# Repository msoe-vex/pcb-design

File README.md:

# PCB and Circuitry Design Repository
This repository is dedicated to storing files required for designing and creating PCBs for our robots. Different projects are put in separate folders, and an included "README.md" file should be included with each project to explain the purpose of each.

## Software Installation
These projects largely use the KiCAD application for circuitry and PCB design. This software can be installed from the following link: 

https://downloads.kicad.org/kicad/windows/explore/nightlies/download/kicad-msvc.r24754.1860893d63-x86_64.exe

**NOTE: We will be using a nightly version until KiCAD 6.00 is released later this year!**

Other versions for various OS platforms can also be found on their website.

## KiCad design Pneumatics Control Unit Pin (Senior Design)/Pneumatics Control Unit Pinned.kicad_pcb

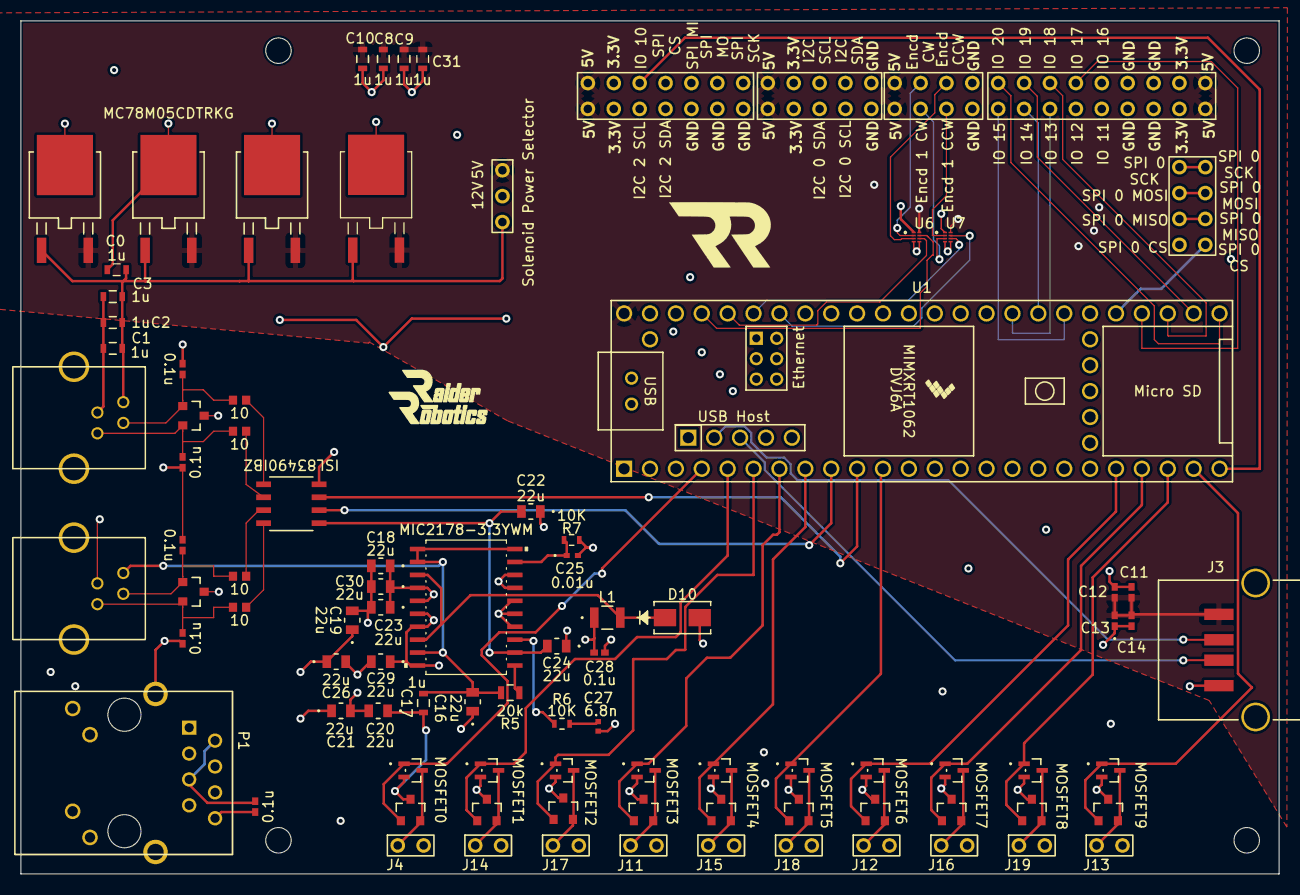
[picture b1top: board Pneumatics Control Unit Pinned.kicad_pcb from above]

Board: 4 copper layers, 123.4 x 83.7 mm, 96 parts (0 on the bottom side), 82 nets.

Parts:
C0, C1, C2, C3, C8, C9, C10, C17, C31: 1u; C1608X7R1C105K080AC
C4, C5, C6, C7, C11, C12, C15, C28: 0.1u; 0402YC104KAT2A
C13, C14: 10n; 0402YC103KAT2A
C16, C18, C19, C20, C21, C22, C23, C24, C26, C29, C30: 22u; CL21A226MQQNNNE
C25: 0.01u; CL05B103KO5NNNC
C27: 6.8n; 0402B682K500CT
D1, D2, D3, D4, D5, D6, D7, D8, D9, D11, D12, D13: PESD1FLEX,215; PESD1FLEX215
D10: CDBA340-HF
H1, H2, H3, H4: MountingHole; MountingHole_2.5mm
J1: RX_PORT; MTJ-642BX2
J2: TX_PORT; MTJ-642BX2
J3: 87583-2010BLF
J4, J11, J12, J13, J14, J15, J16, J17, J18, J19: Conn_01x02_Male; Conn_1x2
J5: GPIO Bank 0; Conn_2x7
J6: SPI 0; Conn_2x4
J7: Solenoid Power Selector; Conn_1x3
J8: GPIO Bank 1; Conn_2x9
J9: I2C 1-2; Conn_2x5
J10: Encoder; Conn_2x4
L1: 33u; LB3218T330K
MOSFET0, MOSFET1, MOSFET2, MOSFET3, MOSFET4, MOSFET5, MOSFET6, MOSFET7, MOSFET8, MOSFET9: SSM3K7002KFU
P1: J1B1211CCD
R1, R2, R3, R4: 10; RNCP0603FTD10R0
R5: 20k; SR1-0805-320
R6, R7: 10K; SR1-0603-310
U0, U2, U3, U4: MC78M05CDTRKG
U1: Teensy4.1; Teensy41
U5: ISL83490IBZ
U6, U7: 74AXP2T3407GSX
U8: MIC2178-3.3YWM; MIC2178-33YWM

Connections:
+3V3: C18.2, C19.2, C20.2, C21.2, C22.2, C23.2, C24.2, C26.2, C28.2, C29.2, C30.2, J5.2, J5.9, J8.2, J8.11, J9.2, J9.7, L1.1, U5.1 (VCC), U6.1 (VCCI), U7.1 (VCCI), U8.12 (FB)
+5V: C8.2, C9.2, C10.2, C11.2, C12.2, C13.2, C14.2, C31.2, J3.4 (VCC), J5.1, J5.8, J7.1, J8.1, J8.10, J9.1, J9.6, J10.1, J10.5, U0.3 (OUTPUT), U1.48 (VIN), U2.3 (OUTPUT), U3.3 (OUTPUT), U4.3 (OUTPUT), U6.8 (VCCO), U7.8 (VCCO)
/Encoder_0_CCW: J10.7, U6.3 (2A)
/Encoder_0_CW: J10.6, U6.2 (1A)
/Encoder_1_CCW: J10.3, U7.2 (1A)
/Encoder_1_CW: J10.2, U7.3 (2A)
/GPIO_0: D3.1, MOSFET0.1 (GATE), U1.4 (2_OUT2)
/GPIO_1: D7.1, MOSFET1.1 (GATE), U1.5 (3_LRCLK2)
/GPIO_2: D11.1, MOSFET2.1 (GATE), U1.6 (4_BCLK2)
/GPIO_3: D4.1, MOSFET3.1 (GATE), U1.7 (5_IN2)
/GPIO_4: D8.1, MOSFET4.1 (GATE), U1.8 (6_OUT1D)
/GPIO_5: D12.1, MOSFET5.1 (GATE), U1.11 (9_OUT1C)
/GPIO_6: D5.1, MOSFET6.1 (GATE), U1.20 (28_RX7)
/GPIO_7: D9.1, MOSFET7.1 (GATE), U1.21 (29_TX7)
/GPIO_8: D13.1, MOSFET8.1 (GATE), U1.22 (30_CRX3)
/GPIO_9: D6.1, MOSFET9.1 (GATE), U1.23 (31_CTX3)
/GPIO_10: J5.10, U1.24 (32_OUT1B)
/GPIO_11: J8.14, U1.37 (15_A1_RX3_SPDIF_IN)
/GPIO_12: J8.15, U1.36 (14_A0_TX3_SPDIF_OUT)
/GPIO_13: J8.16, U1.33 (41_A17)
/GPIO_14: J8.17, U1.32 (40_A16)
/GPIO_15: J8.18, U1.31 (39_MISO1_OUT1A)
/GPIO_16: J8.5, U1.30 (38_CS1_IN1)
/GPIO_17: J8.6, U1.28 (36_CS)
/GPIO_18: J8.7, U1.27 (35_TX8)
/GPIO_19: J8.8, U1.26 (34_RX8)
/GPIO_20: J8.9, U1.25 (33_MCLK2)
/I2C_0_SCL: J9.4, U1.41 (19_A5_SCL)
/I2C_0_SDA: J9.3, U1.40 (18_A4_SDA)
/I2C_1_SCL: J9.8, U1.38 (16_A2_RX4_SCL1)
/I2C_1_SDA: J9.9, U1.39 (17_A3_TX4_SDA1)
/I2C_2_SCL: J5.3, U1.16 (24_A10_TX6_SCL2)
/I2C_2_SDA: J5.4, U1.17 (25_A11_RX6_SDA2)
/LED_Ethernet: P1.10 (GRN+), U1.61 (LED)
/R+_Ethernet: P1.4 (RD+), U1.60 (R+)
/R-_Ethernet: P1.6 (RD-), U1.65 (R-)
/RS485_A_12V: C16.2, C17.2, J1.4, R5.2, U8.1 (VIN), U8.2 (VIN), U8.9 (VIN), U8.20 (EN)
/RS485_B_12V: C0.2, C1.2, C2.2, C3.2, J2.4, J7.3, U0.1 (INPUT), U2.1 (INPUT), U3.1 (INPUT), U4.1 (INPUT)
/RS485_RXD: U1.10 (8_TX2_IN1), U5.3 (DI)
/RS485_TXD: U1.9 (7_RX2_OUT1A), U5.2 (RO)
/SPI_0_CS: J6.4, J6.8, U1.12 (10_CS_MQSR), U1.29 (37_CS)
/SPI_0_MISO: J6.3, J6.7, U1.14 (12_MISO_MQSL)
/SPI_0_MOSI: J6.2, J6.6, U1.13 (11_MOSI_CTX1)
/SPI_0_SCK: J6.1, J6.5, U1.35 (13_SCK_LED)
/SPI_1_CS: J5.11, U1.2 (0_RX1_CRX2_CS1)
/SPI_1_MISO1: J5.12, U1.3 (1_TX1_CTX2_MISO1)
/SPI_1_MOSI1: J5.13, U1.18 (26_A12_MOSI1)
/SPI_1_SCK: J5.14, U1.19 (27_A13_SCK1)
/Solenoid_Power: J4.2, J7.2, J11.2, J12.2, J13.2, J14.2, J15.2, J16.2, J17.2, J18.2, J19.2
/T+_Ethernet: P1.1 (TD+), U1.63 (T+)
/T-_Ethernet: P1.3 (TD-), U1.62 (T-)
/USB_D+: J3.2 (D+), U1.57 (D+)
/USB_D-: J3.3 (D-), U1.56 (D-)
GND: C0.1, C1.1, C2.1, C3.1, C4.1, C5.1, C6.1, C7.1, C8.1, C9.1, C10.1, C11.1, C12.1, C13.1, C14.1, C15.1, C16.1, C17.1, C18.1, C19.1, C20.1, C21.1, C22.1, C23.1, C24.1, C25.2, C26.1, C27.1, C28.1, C29.1, C30.1, C31.1, D1.3, D2.3, D3.3, D4.3, D5.3, D6.3, D7.3, D8.3, D9.3, D10.2, D11.3, D12.3, D13.3, J1.3, J2.3, J3.1 (GND), J5.5, J5.6, J5.7, J8.3, J8.4, J8.12, J8.13, J9.5, J9.10, J10.4, J10.8, MOSFET0.2 (SOURCE), MOSFET1.2 (SOURCE), MOSFET2.2 (SOURCE), MOSFET3.2 (SOURCE), MOSFET4.2 (SOURCE), MOSFET5.2 (SOURCE), MOSFET6.2 (SOURCE), MOSFET7.2 (SOURCE), MOSFET8.2 (SOURCE), MOSFET9.2 (SOURCE), P1.7 (NC), P1.8 (GH_GND@1), P1.9 (GRN-), P1.11 (YLW-), P1.12 (YLW+), P1.13 (CH_GND@2), P1.14 (CH_GND@3), R7.2, U0.4 (GROUND), U1.1 (GND), U1.34 (GND), U1.47 (GND), U1.50 (VBAT), U1.51 (3V3), U1.52 (GND), U1.53 (PROGRAM), U1.54 (ON_OFF), U1.58 (GND), U1.59 (GND), U1.64 (GND), U2.4 (GROUND), U3.4 (GROUND), U4.4 (GROUND), U5.4 (GND), U6.4 (GND), U6.5 (GND), U7.4 (GND), U7.5 (GND), U8.4 (PGND), U8.5 (PGND), U8.6 (PGND), U8.7 (PGND), U8.10 (*PWM), U8.14 (SGND), U8.15 (SGND), U8.16 (SGND), U8.17 (SGND), U8.18 (SYNC)
unnamed: C4.2, D1.1, J1.2, R2.1
unnamed: C5.2, D2.1, J2.2, R4.1
unnamed: C6.2, D1.2, J1.1, R1.1
unnamed: C7.2, D2.2, J2.1, R3.1
unnamed: C27.2, R6.2
unnamed: D3.2, J4.1, MOSFET0.3 (DRAIN)
unnamed: D4.2, J11.1, MOSFET3.3 (DRAIN)
unnamed: D5.2, J12.1, MOSFET6.3 (DRAIN)
unnamed: D6.2, J13.1, MOSFET9.3 (DRAIN)
unnamed: D7.2, J14.1, MOSFET1.3 (DRAIN)
unnamed: D8.2, J15.1, MOSFET4.3 (DRAIN)
unnamed: D9.2, J16.1, MOSFET7.3 (DRAIN)
unnamed: D11.2, J17.1, MOSFET2.3 (DRAIN)
unnamed: D12.2, J18.1, MOSFET5.3 (DRAIN)
unnamed: D13.2, J19.1, MOSFET8.3 (DRAIN)
unnamed: C15.2, P1.2 (TCT), P1.5 (RCT)
unnamed: U1.42 (20_A6_TX5_LRCLK1), U7.7 (1Y)
unnamed: U1.43 (21_A7_RX5_BCLK1), U7.6 (2Y)
unnamed: U1.44 (22_A8_CTX1), U6.6 (2Y)
unnamed: U1.45 (23_A9_CRX1_MCLK1), U6.7 (1Y)
unnamed: R1.2, U5.8 (A)
unnamed: R2.2, U5.7 (B)
unnamed: R4.2, U5.5 (Y)
unnamed: R3.2, U5.6 (Z)
unnamed: C25.1, R7.1, U8.19 (BIAS)
unnamed: R6.1, U8.13 (COMP)
unnamed: R5.1, U8.11 (PWRGD)
unnamed: D10.1, L1.2, U8.3 (SW), U8.8 (SW)

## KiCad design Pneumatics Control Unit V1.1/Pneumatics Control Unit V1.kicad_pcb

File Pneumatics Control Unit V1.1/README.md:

# Pneumatic Control Unit
This project is dedicated to creating a board that can control 8 pneumatic devices running at either 5V or 12V from the VEX V5 brain. We take power from the smart ports to power the pneumatics, then based on the jumpers will step down the voltage to 5V or keep it at 12V. The signal sent to the board will be read by a MicoMod teensy and will then send a signal to the corresponding pneumatic device. The transmit port is for future versions.

### Project Information
This board was originally created by Nathan Roth and Asher Sprigler, with assistance provided by Andrew Kempen in the 2021-2022 VEX season.

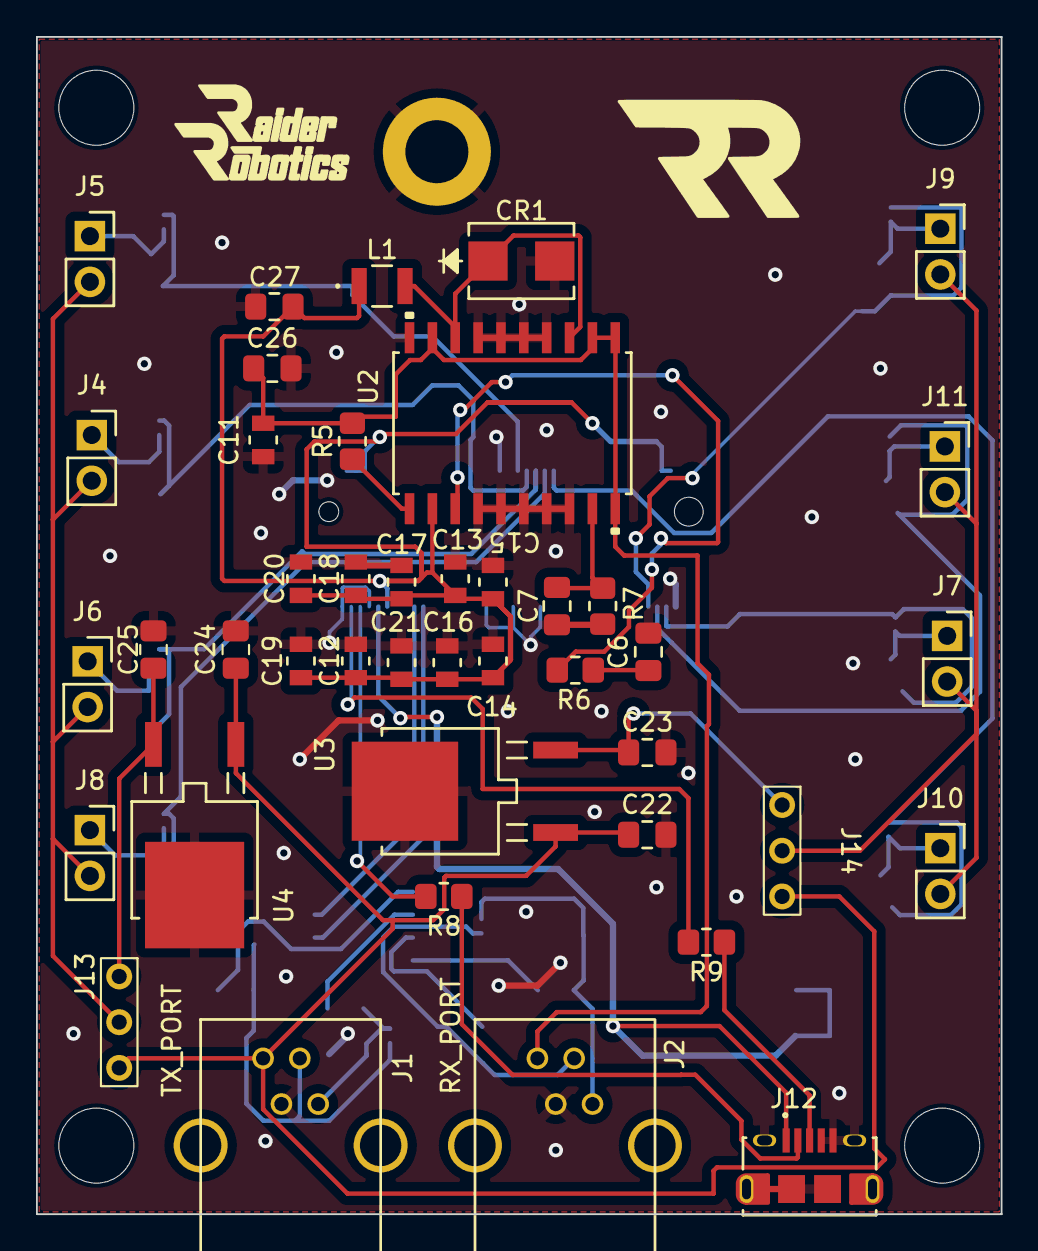
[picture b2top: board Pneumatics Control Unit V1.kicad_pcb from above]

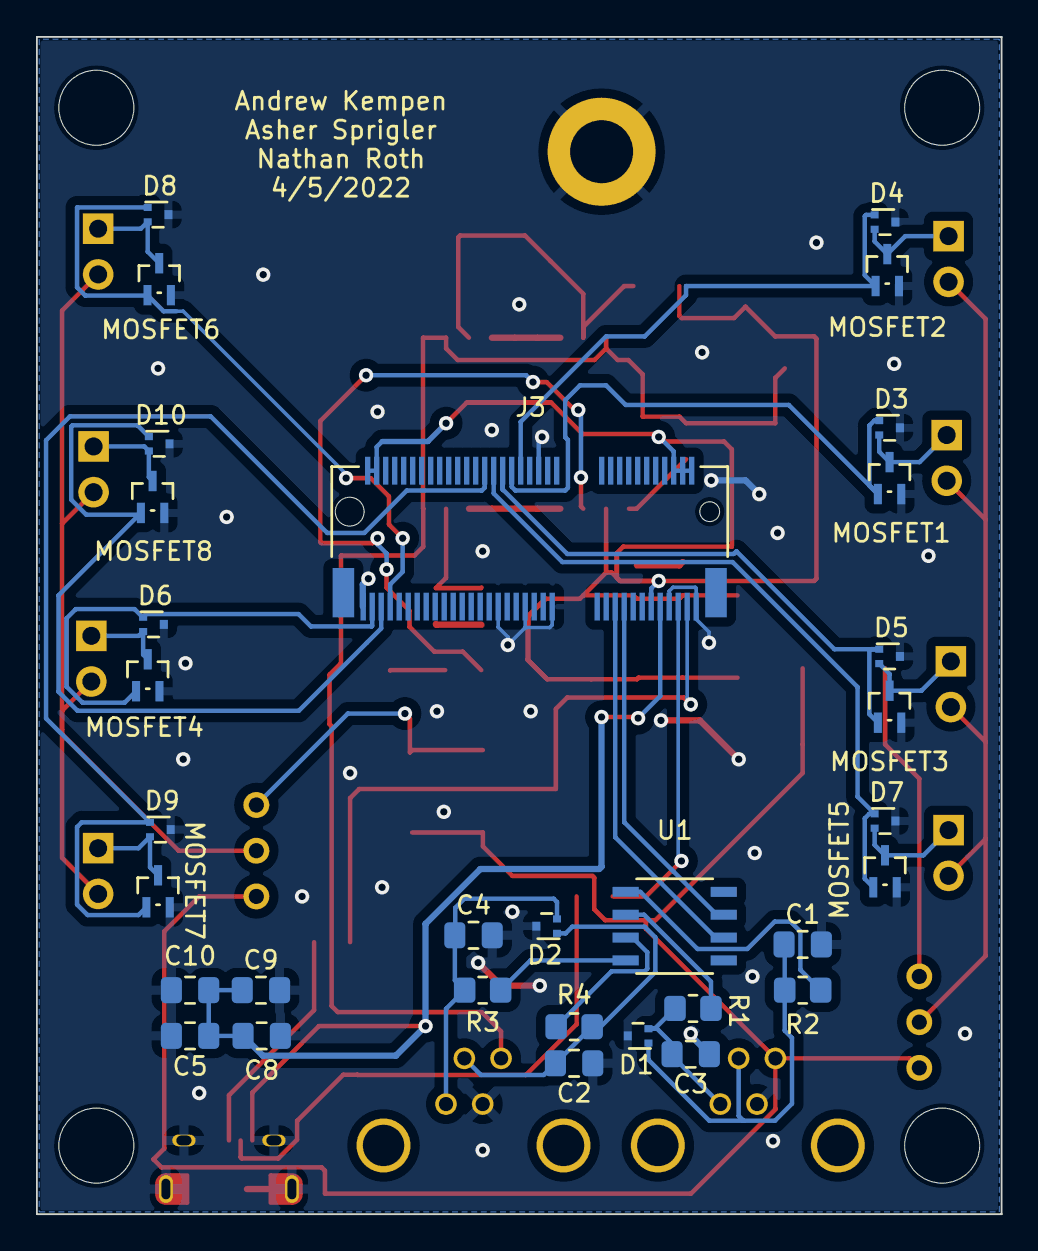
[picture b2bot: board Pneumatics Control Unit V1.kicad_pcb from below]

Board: 4 copper layers, 53.6 x 65.4 mm, 79 parts (33 on the bottom side), 44 nets.

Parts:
C1, C2, C3, C4, C9, C10, C27: 0.1u; C_0805_2012Metric_Pad1.18x1.45mm_HandSolder
C5, C8: 10n; C_0805_2012Metric_Pad1.18x1.45mm_HandSolder
C6: 6.8n; C_0805_2012Metric_Pad1.18x1.45mm_HandSolder
C7: 0.01u; C_0805_2012Metric_Pad1.18x1.45mm_HandSolder
C11: CL21A226MQQNNNF (22uF); CL21A226MQQNNNF
C12, C13, C14, C15, C16, C17, C18, C19, C20, C21: 22uF; CL21A226MQQNNNF
C22, C23, C24, C25, C26: 1u; C_0805_2012Metric_Pad1.18x1.45mm_HandSolder
CR1: MBRS130L
D1, D2, D3, D4, D5, D6, D7, D8, D9, D10: D_TVS_x2_AAC; SOT-723
H1, H2, H3, H4: MountingHole; MountingHole_2.5mm
H5: STAND-OFF-REFLOW2.5MM_TALL; STAND-OFF-REFLOW-M2.5
J1: TX_PORT; RS485
J2: RX_PORT; RS485
J3: MICROMOD-2222; M.2-CONNECTOR-E
J4, J5, J6, J7, J8, J9, J10, J11: Conn_01x02_Male; PinSocket_1x02_P2.54mm_Vertical
J12: 10118194-0001LF; AMPHENOL_10118194-0001LF
J13, J14: Conn_01x03_Male; Conn_1x3
L1: LB3218T330M (33uH); LB3218T330M
MOSFET1, MOSFET2, MOSFET3, MOSFET4, MOSFET5, MOSFET6, MOSFET7, MOSFET8: SSM3K7002KFU
R1, R2, R3, R4: 10; R_0805_2012Metric_Pad1.20x1.40mm_HandSolder
R5: 20k; R_0805_2012Metric_Pad1.20x1.40mm_HandSolder
R6, R7: 10k; R_0805_2012Metric_Pad1.20x1.40mm_HandSolder
R8, R9: 27; R_0805_2012Metric_Pad1.20x1.40mm_HandSolder
U1: ISL83490IBZ
U2: MIC2178-3.3YWM
U3, U4: MC78M05CDTRKG

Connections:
/220uF: C12.1, C13.1, C14.1, C15.1, C16.1, C17.1, C18.1, C19.1, C20.1, C21.1, C27.1, J3.2 (3.3V), J3.4 (3.3V_EN), J3.6 (~RESET), J3.11 (~BOOT), J3.72 (RTC_3V), J3.74 (3.3V), L1.1, U2.12 (FB)
/GPIO_0: D4.1 (A1), J3.40 (G0/BUS0), MOSFET2.1 (GATE)
/GPIO_1: D3.1 (A1), J3.42 (G1/BUS1), MOSFET1.1 (GATE)
/GPIO_2: D5.1 (A1), J3.44 (G2/BUS2), MOSFET3.1 (GATE)
/GPIO_3: D7.1 (A1), J3.46 (G3/BUS3), MOSFET5.1 (GATE)
/GPIO_4: D9.1 (A1), J3.48 (G4/BUS4), MOSFET7.1 (GATE)
/GPIO_5: D6.1 (A1), J3.73 (G5/BUS5), MOSFET4.1 (GATE)
/GPIO_6: D10.1 (A1), J3.71 (G6/BUS6), MOSFET8.1 (GATE)
/GPIO_7: D8.1 (A1), J3.69 (G7/BUS7), MOSFET6.1 (GATE)
/RS485_A_12V: C11.1, C26.1, J2.4, R5.2, U2.1 (VIN), U2.2 (VIN), U2.9 (VIN), U2.20 (EN)
/RS485_B_12V: C22.1, C24.1, J1.4, J13.3, J14.3, U3.1 (INPUT), U4.1 (INPUT)
/RS485_RXD: J3.17 (TX1), U1.3 (DI)
/RS485_TXD: J3.19 (RX1), U1.2 (RO)
/USB_D+: J3.3 (USB_D+), R9.2
/USB_D-: J3.5 (USB_D-), R8.2
/solenoid_power: J4.2, J5.2, J6.2, J8.2, J13.2
/solenoid_power_2: J7.2, J9.2, J10.2, J11.2, J14.2
GND: C1.2, C2.2, C3.2, C4.2, C5.2, C6.2, C7.2, C8.2, C9.2, C10.2, C11.2, C12.2, C13.2, C14.2, C15.2, C16.2, C17.2, C18.2, C19.2, C20.2, C21.2, C22.2, C23.2, C24.2, C25.2, C26.2, C27.2, CR1.2, D1.3 (common), D2.3 (common), D3.3 (common), D4.3 (common), D5.3 (common), D6.3 (common), D7.3 (common), D8.3 (common), D9.3 (common), D10.3 (common), H5.1, J1.3, J2.3, J3.1 (GND), J3.7 (GND), J3.33 (GND), J3.36 (GND), J3.39 (GND), J3.45 (GND), J3.75 (GND), J12.4, J12.5, J12.S1 (SHIELD), J12.S2 (SHIELD), J12.S3 (SHIELD), J12.S4 (SHIELD), J12.S5 (SHIELD), J12.S6 (SHIELD), MOSFET1.2 (SOURCE), MOSFET2.2 (SOURCE), MOSFET3.2 (SOURCE), MOSFET4.2 (SOURCE), MOSFET5.2 (SOURCE), MOSFET6.2 (SOURCE), MOSFET7.2 (SOURCE), MOSFET8.2 (SOURCE), R7.2, U2.4 (PGND), U2.5 (PGND), U2.6 (PGND), U2.7 (PGND), U2.10 (*PWM), U2.14 (SGND), U2.15 (SGND), U2.16 (SGND), U2.17 (SGND), U2.18 (SYNC), U3.4 (GROUND), U4.4 (GROUND)
unnamed: C6.1, R6.2
unnamed: C5.1, C8.1, C9.1, C10.1
unnamed: C1.1, D1.1 (A1), J1.2, R2.1
unnamed: C3.1, D1.2 (A2), J1.1, R1.1
unnamed: C2.1, D2.1 (A1), J2.2, R4.1
unnamed: C4.1, D2.2 (A2), J2.1, R3.1
unnamed: D3.2 (A2), J4.1, MOSFET1.3 (DRAIN)
unnamed: D4.2 (A2), J5.1, MOSFET2.3 (DRAIN)
unnamed: D5.2 (A2), J6.1, MOSFET3.3 (DRAIN)
unnamed: D6.2 (A2), J7.1, MOSFET4.3 (DRAIN)
unnamed: D7.2 (A2), J8.1, MOSFET5.3 (DRAIN)
unnamed: D8.2 (A2), J9.1, MOSFET6.3 (DRAIN)
unnamed: D9.2 (A2), J10.1, MOSFET7.3 (DRAIN)
unnamed: D10.2 (A2), J11.1, MOSFET8.3 (DRAIN)
unnamed: J12.2, R8.1
unnamed: J12.3, R9.1
unnamed: R3.2, U1.8 (A)
unnamed: R4.2, U1.7 (B)
unnamed: R2.2, U1.5 (Y)
unnamed: R1.2, U1.6 (Z)
unnamed: C7.1, R7.1, U2.19 (BIAS)
unnamed: R6.1, U2.13 (COMP)
unnamed: R5.1, U2.11 (PWRGD)
unnamed: CR1.1, L1.2, U2.3 (SW), U2.8 (SW)
unnamed: C23.1, U3.3 (OUTPUT)
unnamed: C25.1, U4.3 (OUTPUT)

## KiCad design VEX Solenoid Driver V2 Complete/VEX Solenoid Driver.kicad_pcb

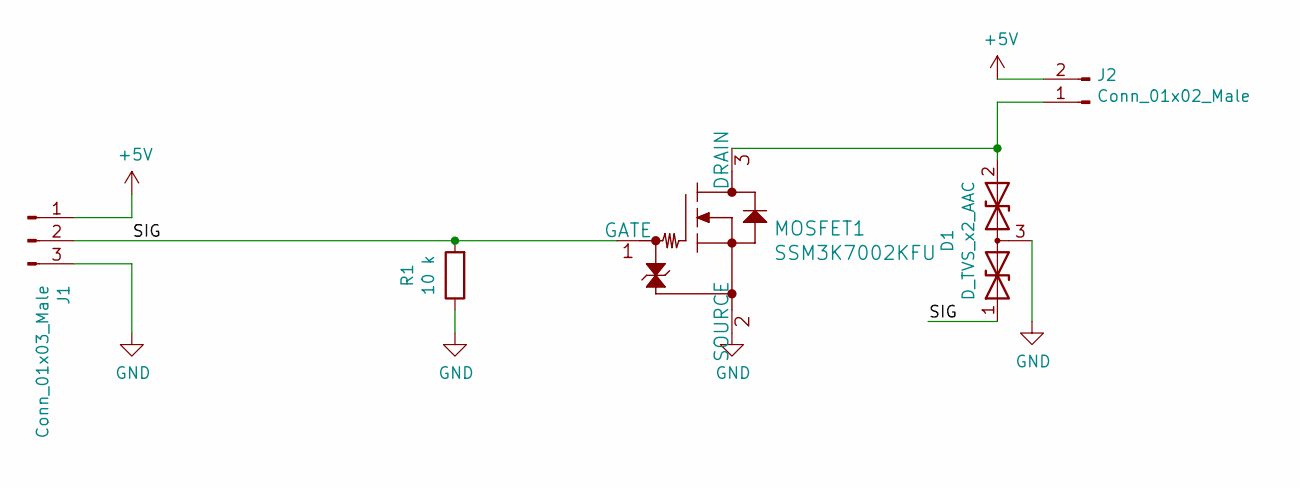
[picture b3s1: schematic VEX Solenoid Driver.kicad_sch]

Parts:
D1: D_TVS_x2_AAC; SOT-723
J1: Conn_01x03_Male; PinSocket_1x03_P2.54mm_Vertical
J2: Conn_01x02_Male; PinSocket_1x02_P2.54mm_Vertical
MOSFET1: SSM3K7002KFU
R1: 10 k; R_0805_2012Metric_Pad1.20x1.40mm_HandSolder

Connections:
+5V: J1.1, J2.2
/SIG: D1.1 (A1), J1.2, MOSFET1.1 (GATE), R1.2
GND: D1.3 (common), J1.3, MOSFET1.2 (SOURCE), R1.1
unnamed: D1.2 (A2), J2.1, MOSFET1.3 (DRAIN)

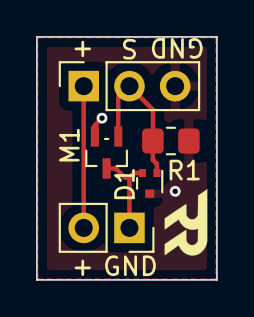
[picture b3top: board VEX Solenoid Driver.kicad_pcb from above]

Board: 2 copper layers, 10.0 x 13.5 mm, 5 parts (0 on the bottom side), 4 nets.

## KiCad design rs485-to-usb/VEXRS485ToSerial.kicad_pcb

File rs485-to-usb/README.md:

# RS-485 to USB Serial Board
This project is dedicated to creating a board that can interface between the smart ports on the V5 Robot Brain and the USB of our co-processor, which requires converting two RS-485 channels (one RX, one TX) into USB Serial.

### Project Information
This board was originally created by Andrew Kempen during the 2020-2021 VEX ChangeUp season.

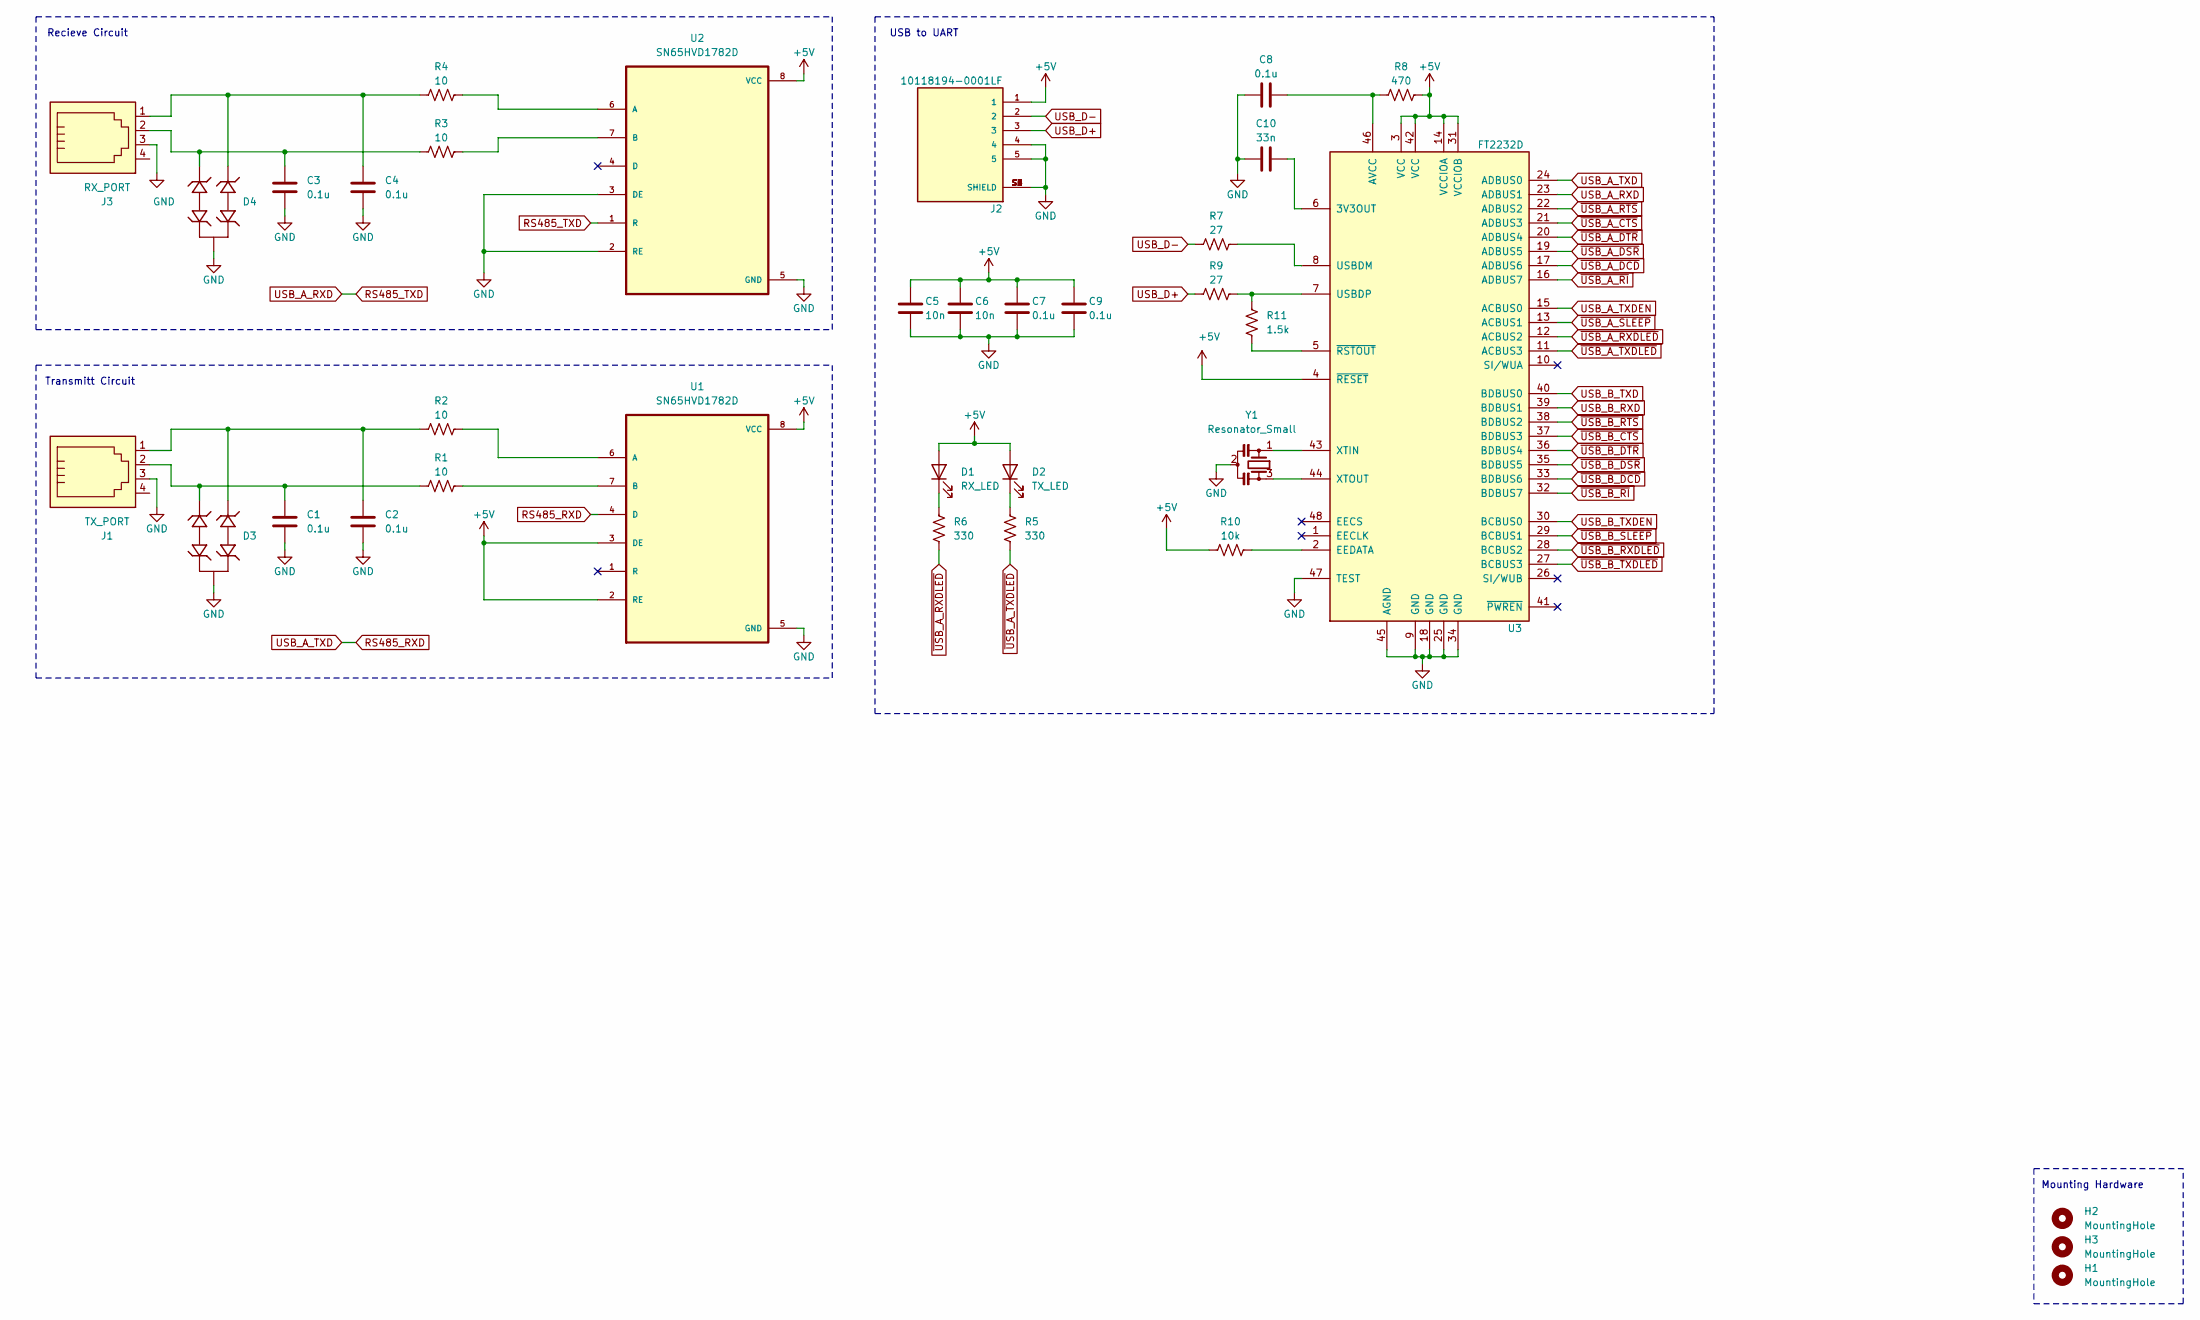
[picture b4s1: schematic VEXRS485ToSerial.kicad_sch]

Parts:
C1, C2, C3, C4, C7, C8, C9: 0.1u; C_0805_2012Metric_Pad1.18x1.45mm_HandSolder
C5, C6: 10n; C_0805_2012Metric_Pad1.18x1.45mm_HandSolder
C10: 33n; C_0805_2012Metric_Pad1.18x1.45mm_HandSolder
D1: RX_LED; LED_0805_2012Metric_Pad1.15x1.40mm_HandSolder
D2: TX_LED; LED_0805_2012Metric_Pad1.15x1.40mm_HandSolder
D3, D4: CDSOT23-SM712; SOT-23-3
H1, H2, H3: MountingHole; MountingHole_2.5mm
J1: TX_PORT; C189737
J2: 10118194-0001LF; AMPHENOL_10118194-0001LF
J3: RX_PORT; C189737
R1, R2, R3, R4: 10; R_0805_2012Metric_Pad1.20x1.40mm_HandSolder
R5, R6: 330; R_0805_2012Metric_Pad1.20x1.40mm_HandSolder
R7, R9: 27; R_0805_2012Metric_Pad1.20x1.40mm_HandSolder
R8: 470; R_0805_2012Metric_Pad1.20x1.40mm_HandSolder
R10: 10k; R_0805_2012Metric_Pad1.20x1.40mm_HandSolder
R11: 1.5k; R_0805_2012Metric_Pad1.20x1.40mm_HandSolder
U1, U2: SN65HVD1782D; SOIC127P599X175-8N
U3: FT2232D; LQFP-48_7x7mm_P0.5mm
Y1: Resonator_Small; OSC_CSTCE16M0V53-R0

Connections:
+5V: C5.1, C6.1, C7.1, C9.1, D1.2 (A), D2.2 (A), J2.1, R8.2, R10.1, U1.2 (RE), U1.3 (DE), U1.8 (VCC), U2.8 (VCC), U3.3 (VCC), U3.4 (~RESET), U3.14 (VCCIOA), U3.31 (VCCIOB), U3.42 (VCC)
GND: C1.2, C2.2, C3.2, C4.2, C5.2, C6.2, C7.2, C8.1, C9.2, C10.1, D3.3, D4.3, J1.3, J2.4, J2.5, J2.S1 (SHIELD), J2.S2 (SHIELD), J2.S3 (SHIELD), J2.S4 (SHIELD), J2.S5 (SHIELD), J2.S6 (SHIELD), J3.3, U1.5 (GND), U2.2 (RE), U2.3 (DE), U2.5 (GND), U3.9 (GND), U3.18 (GND), U3.25 (GND), U3.34 (GND), U3.45 (AGND), U3.47 (TEST), Y1.2
unnamed: C8.2, R8.1, U3.46 (AVCC)
unnamed: C10.2, U3.6 (3V3OUT)
unnamed: D1.1 (K), R6.1
unnamed: D2.1 (K), R5.1
unnamed: C1.1, D3.1, J1.2, R1.1
unnamed: C2.1, D3.2, J1.1, R2.1
unnamed: C3.1, D4.1, J3.2, R3.1
unnamed: C4.1, D4.2, J3.1, R4.1
unnamed: R4.2, U2.6 (A)
unnamed: R3.2, U2.7 (B)
unnamed: R7.2, U3.8 (USBDM)
unnamed: R9.2, R11.1, U3.7 (USBDP)
unnamed: R10.2, U3.2 (EEDATA)
unnamed: R11.2, U3.5 (~RSTOUT)
unnamed: R2.2, U1.6 (A)
unnamed: R1.2, U1.7 (B)
unnamed: U3.43 (XTIN), Y1.1
unnamed: U3.44 (XTOUT), Y1.3
RS485_RXD: U1.4 (D), U3.24 (ADBUS0)
RS485_TXD: U2.1 (R), U3.23 (ADBUS1)
USB_A_TXDEN: U3.15 (ACBUS0)
USB_B_RXD: U3.39 (BDBUS1)
USB_B_TXD: U3.40 (BDBUS0)
USB_B_TXDEN: U3.30 (BCBUS0)
USB_D+: J2.3, R9.1
USB_D-: J2.2, R7.1
~USB_A_CTS: U3.21 (ADBUS3)
~USB_A_DCD: U3.17 (ADBUS6)
~USB_A_DSR: U3.19 (ADBUS5)
~USB_A_DTR: U3.20 (ADBUS4)
~USB_A_RI: U3.16 (ADBUS7)
~USB_A_RTS: U3.22 (ADBUS2)
~USB_A_RXDLED: R6.2, U3.12 (ACBUS2)
~USB_A_SLEEP: U3.13 (ACBUS1)
~USB_A_TXDLED: R5.2, U3.11 (ACBUS3)
~USB_B_CTS: U3.37 (BDBUS3)
~USB_B_DCD: U3.33 (BDBUS6)
~USB_B_DSR: U3.35 (BDBUS5)
~USB_B_DTR: U3.36 (BDBUS4)
~USB_B_RI: U3.32 (BDBUS7)
~USB_B_RTS: U3.38 (BDBUS2)
~USB_B_RXDLED: U3.28 (BCBUS2)
~USB_B_SLEEP: U3.29 (BCBUS1)
~USB_B_TXDLED: U3.27 (BCBUS3)

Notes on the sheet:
Recieve Circuit
Transmitt Circuit
USB to UART
Mounting Hardware

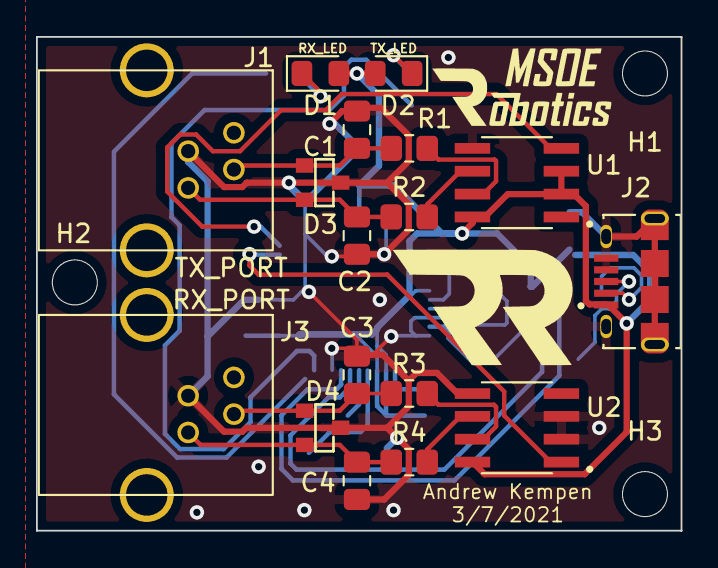
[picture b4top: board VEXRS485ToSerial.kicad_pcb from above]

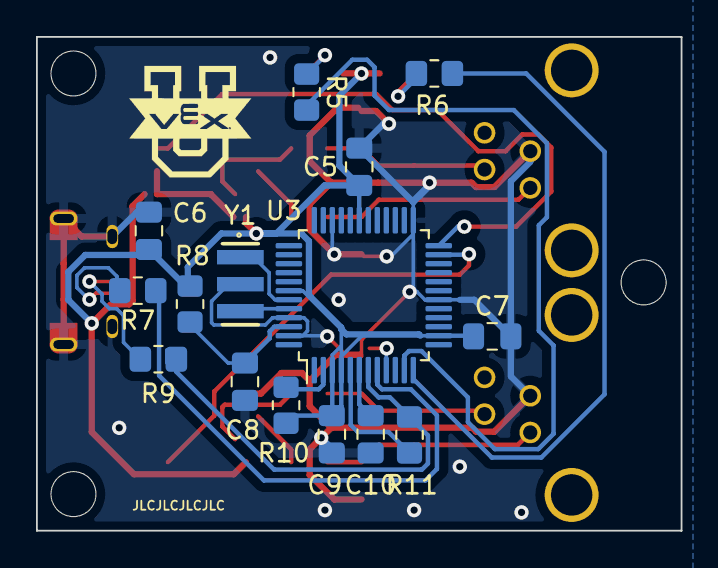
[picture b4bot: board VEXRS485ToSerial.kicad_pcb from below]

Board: 2 copper layers, 35.8 x 27.4 mm, 35 parts (15 on the bottom side), 26 nets.

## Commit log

2021-10-22 Added files for the rs485 to USB serial board
2022-03-22 Add Pneumatics V1 schematics + PCB design
2022-03-23 using a new chip for RS485 to UART
2022-03-25 Cleaning up the schematic
2022-03-25 Adding voltage converters
2022-03-26 Changing to net labels
2022-03-26 Adding m.2
2022-03-27 Switching linear 3.3 to switching 3.3
2022-03-27 Cleaning
2022-03-29 Uploading Solenoid Driver Files
2022-03-30 Linking foot prints
2022-03-30 Adding USB for programming, Removing linear 5V, standardizing diodes, cleaning up capcitors
2022-03-30 Footprint fun
2022-03-30 Adding back the 5V linear regulator
2022-03-30 Small amount of cleaning up
2022-03-30 Adding better m.2 connector
2022-04-02 PCB Fun times :)
2022-04-02 Consolidated PCB
2022-04-05 Technically its wired
    This is a little messy, but it is wired
2022-04-05 Cleaning up grounds
2022-04-06 Fixing errors and adding another 5V
2022-04-06 Fixing the PCB silkscreen
2022-04-06 Adding some caps to the switching and clearing errors
2022-04-06 Slimming the rectangle
2022-04-06 Removing random line
2022-04-06 Senior Design Upload
2022-04-06 Reducing vias, Thicken traces, adding resistors
2022-04-06 Moved via, cleaning traces
2022-04-06 adding the mosfet silkscreens back
2022-04-06 Removing more vias
2022-04-06 Connecting grounds
2022-04-06 Removing that via
2022-04-06 Making Lines THICK
2022-04-07 Updated Senior Design PCB 0.9
2022-04-07 Adding more grounding vias, and making the mouting holes 8-32
2022-04-09 Senior Update
2022-04-12 Adding Raider Robotics, removing Vex U
2022-04-20 Adding 12V capabilities
2022-04-26 Fixing a few ghosts from old projects, and adding inner copper
2022-07-07 Adding current draw on 5v rail
2022-07-14 Initial wiring, adding another 5V regulator for the GPIO pins, renumbered the mosfets
2022-07-14 Moving labels
2022-07-14 Adding labels for pinouts
2022-07-14 fixing holes labels
2022-07-19 Fixing up the DRC issues
2022-09-17 Fixing some smaller issues
    Removed isolated zones. Fixed some error classes
2022-09-17 Changes to the Gen 3
2022-09-30 Fixing the decoupling capacitor placement
2022-10-06 Adding inner ground planes. This baby grounded now
2022-10-06 Moving the caps, so they decouple

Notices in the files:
parts and their libraries:
Copyright 2021 Accelerated Designs. All rights reserved.
